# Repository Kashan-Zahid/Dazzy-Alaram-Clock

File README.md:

# Dazzy-Alaram

A custom-built desktop alarm clock powered by a Seeed Studio XIAO microcontroller and mechanical key switches. Built for DIY.

## Overview
Dazzy-Alaram is a custom hardware project designed from scratch. It combines a custom printed circuit board (PCB), mechanical switches for tactile input, and a 3D-printed enclosure to create a clean, functional desk clock.

*(Firmware disclosure: AI was used to assist in writing portions of the firmware code).*

---

## Project Gallery & Documentation

### 1. Overall Clock Concept
> 

### 2. Schematic
> 

### 3. PCB Layout
> 

---

## Bill of Materials (BOM)
The complete part list can be found in [`blare alaram.csv`](./blare%20alaram.csv). Key components include:
* Seeed Studio XIAO Microcontroller
* Mechanical Key Switches
* Custom 3D Printed Enclosure parts (Top & Bottom covers)
*

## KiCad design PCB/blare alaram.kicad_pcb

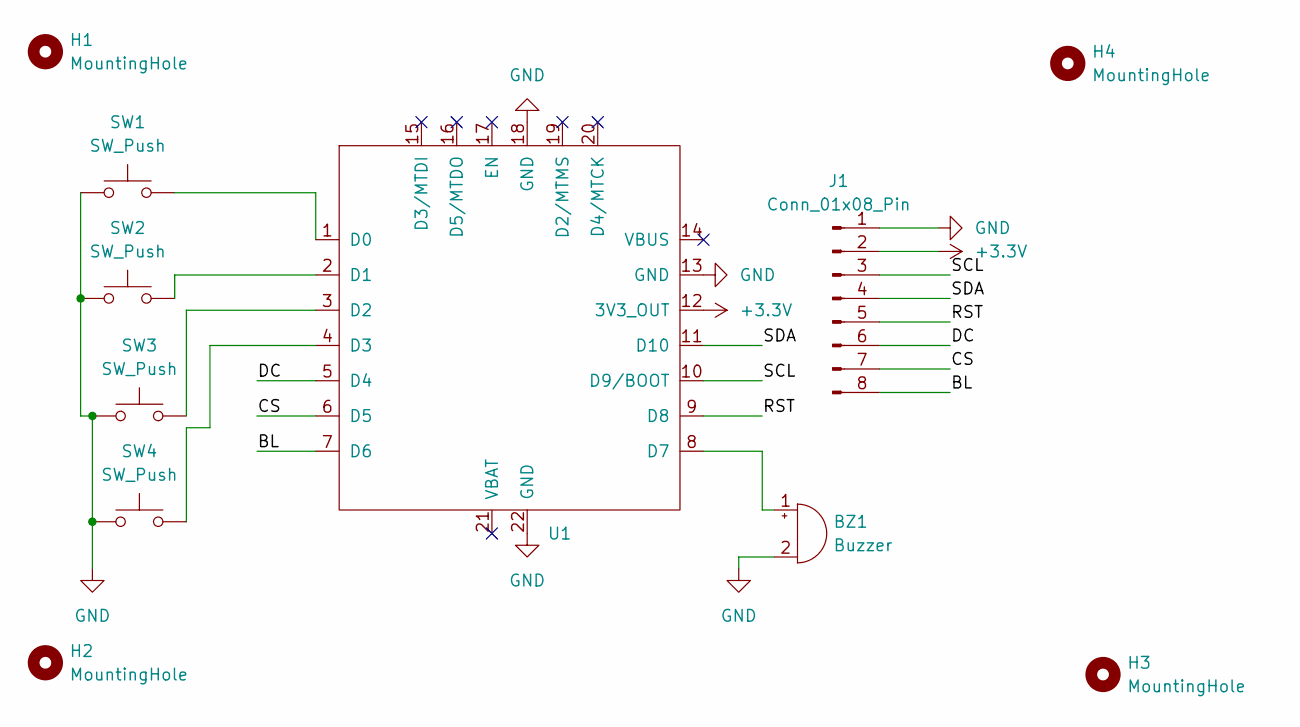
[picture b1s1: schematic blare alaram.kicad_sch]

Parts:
BZ1: Buzzer; Buzzer_12x9.5RM7.6
H1, H2, H3, H4: MountingHole; MountingHole_3.2mm_M3
J1: Conn_01x08_Pin; PinSocket_1x08_P2.54mm_Vertical
SW1, SW2, SW3, SW4: SW_Push; SW_Cherry_MX_1.00u_PCB
U1: XIAO-ESP32-C3-SMD; MCU_Seeed_ESP32C3

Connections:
+3.3V: J1.2, U1.12 (3V3_OUT)
/BL: J1.8, U1.7 (D6)
/CS: J1.7, U1.6 (D5)
/DC: J1.6, U1.5 (D4)
/RST: J1.5, U1.9 (D8)
/SCL: J1.3, U1.10 (D9/BOOT)
/SDA: J1.4, U1.11 (D10)
GND: BZ1.2 (-), J1.1, SW1.1, SW2.1, SW3.1, SW4.1, U1.13 (GND), U1.18 (GND), U1.22 (GND)
unnamed: BZ1.1 (+), U1.8 (D7)
unnamed: SW1.2, U1.1 (D0)
unnamed: SW2.2, U1.2 (D1)
unnamed: SW3.2, U1.3 (D2)
unnamed: SW4.2, U1.4 (D3)

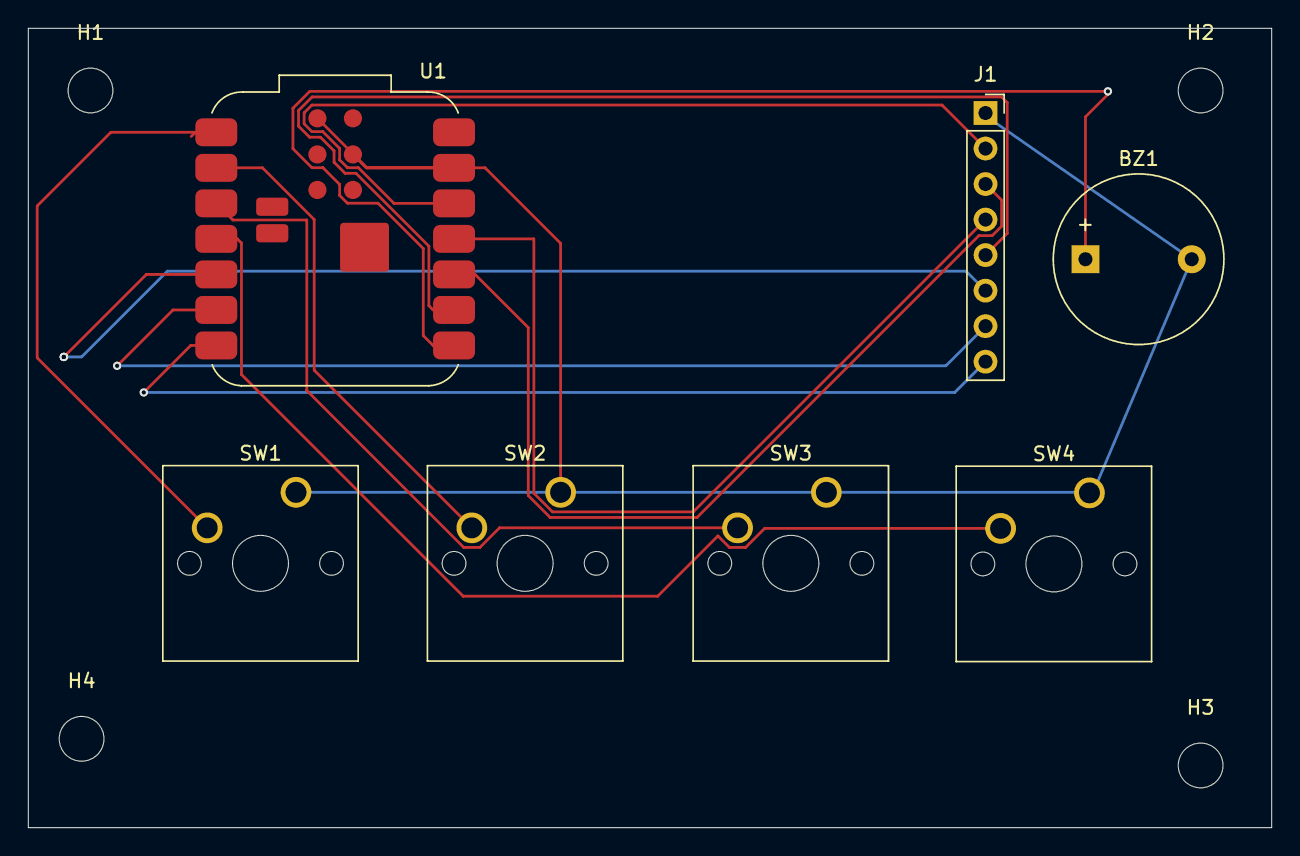
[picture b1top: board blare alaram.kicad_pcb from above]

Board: 2 copper layers, 88.9 x 57.2 mm, 11 parts (0 on the bottom side), 13 nets.

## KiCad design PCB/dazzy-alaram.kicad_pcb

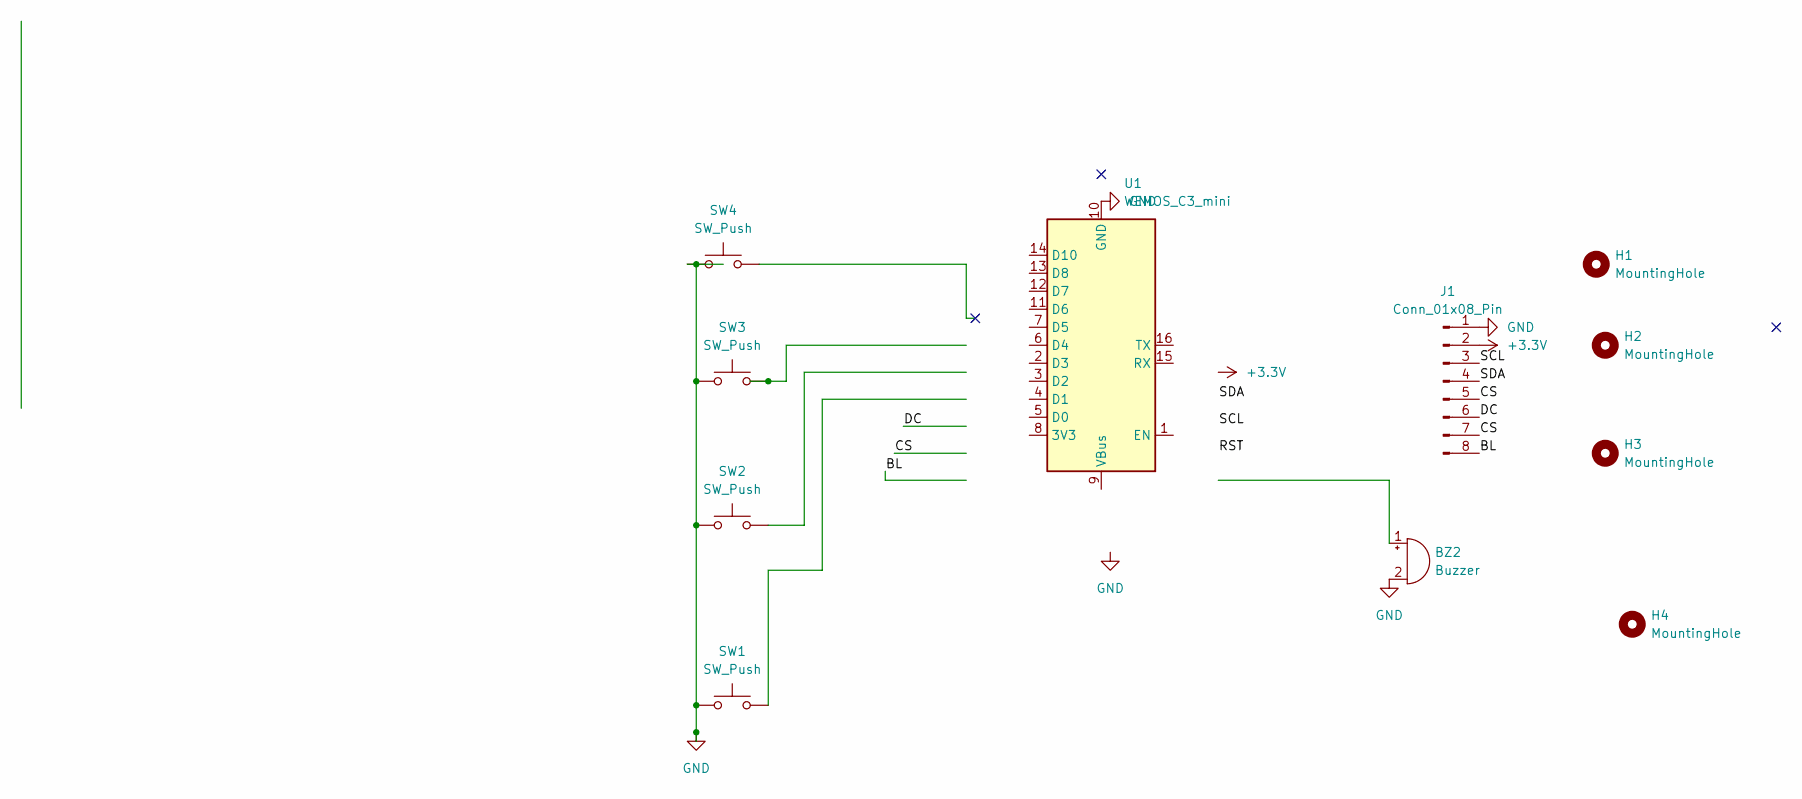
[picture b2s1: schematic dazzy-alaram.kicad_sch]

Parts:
BZ2: Buzzer; Buzzer_12x9.5RM7.6
H1, H2, H3, H4: MountingHole; MountingHole_2.5mm
J1: Conn_01x08_Pin; PinHeader_1x08_P2.54mm_Vertical
SW1, SW2, SW3, SW4: SW_Push; SW_PUSH_6mm
U1: WEMOS_C3_mini

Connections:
+3.3V: J1.2; also elsewhere on the board
/BL: J1.8; also elsewhere on the board
/CS: J1.5, J1.7; also elsewhere on the board
/DC: J1.6; also elsewhere on the board
/SCL: J1.3; also elsewhere on the board
/SDA: J1.4; also elsewhere on the board
GND: BZ2.2 (-_2), J1.1, SW1.1 (1_1), SW2.1 (1_1), SW3.1 (1_1), SW4.1 (1_1), U1.10 (GND); also elsewhere on the board

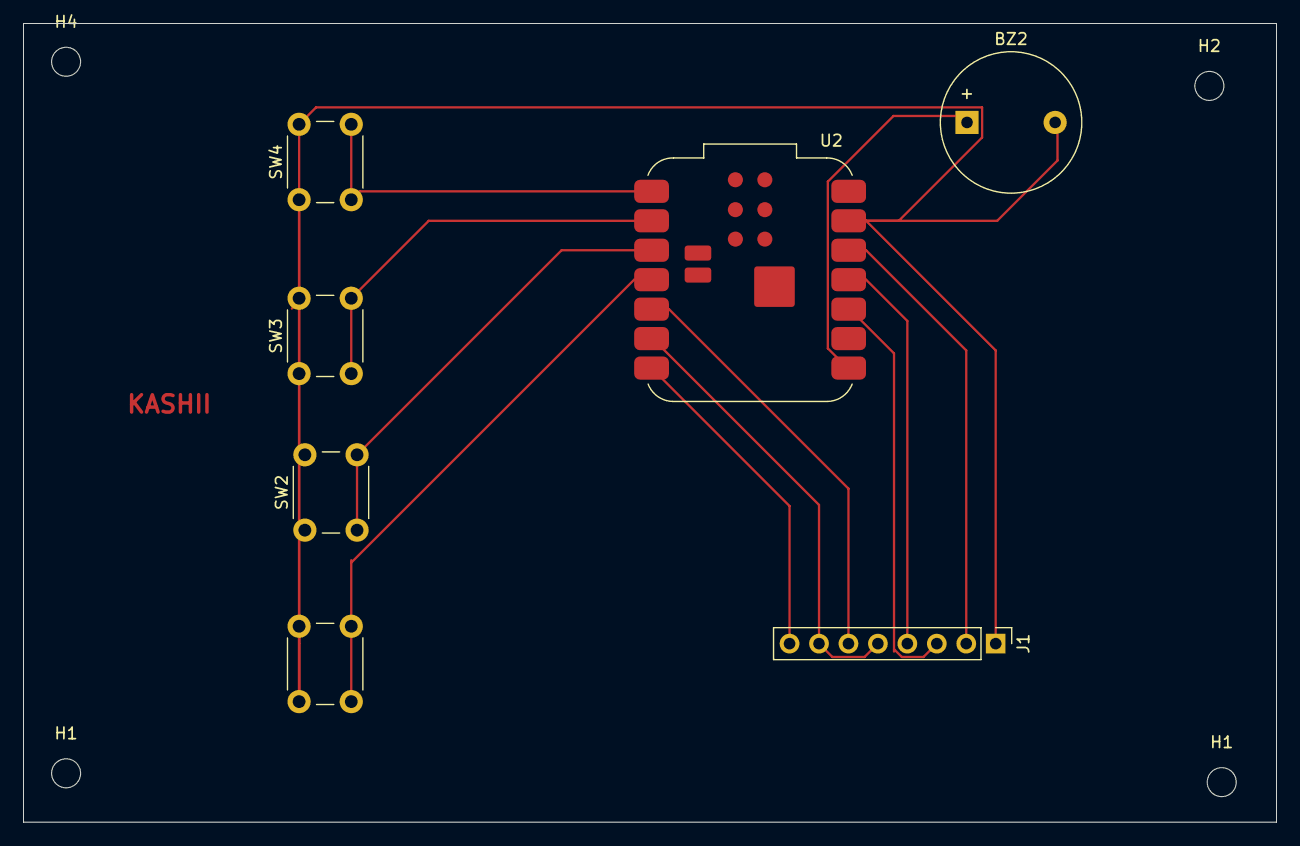
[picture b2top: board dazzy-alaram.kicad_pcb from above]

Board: 2 copper layers, 108.1 x 68.9 mm, 12 parts (0 on the bottom side), 7 nets.

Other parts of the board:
H1#2: MountingHole; MountingHole_2.5mm
U2: XIAO ESP32C3; MCU_Seeed_ESP32C3

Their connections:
+3.3V: U2.12 (VCC_3V3); also elsewhere on the board
/BL: U2.7 (D6); also elsewhere on the board
/CS: U2.6 (D5); also elsewhere on the board
/DC: U2.5 (D4); also elsewhere on the board
/SCL: U2.10 (D9); also elsewhere on the board
/SDA: U2.11 (D10); also elsewhere on the board
GND: U2.13 (GND); also elsewhere on the board
